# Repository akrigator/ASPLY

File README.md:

ASPLY
=====

Control block for  the 'Kronasteel Gala 600 inox' kitche hood based on atmega8/48/88/168/328 microcontroller

#Functions:
1. Manage light;
2. Manage 3 speed fan;
3. Adjustable timers for light and fan.

#Timer activation:
1. Hold one of channel button (light or fan speeds)  about 2,5 second till LED indicator starts blink (0.5 sec in turn on and 0.5 sec in turn off state);
2. Count 3 blinks of indicator to set timer for 30 minutes (each blink = 10 minutes);
3. Release the button - the channel function is activated, indicator blinks with low intencive (1 sec in turn on and 1 sec in turn off state) till timer is stopped;
4. Timer can be disabled by clicking same button again;

#Power cord pinout:
1. grey
2. brown
3. black - fan 3
4. blue - fan 2
5. red - fan 1
6. white - light

#Usefull link:
1. https://github.com/MCUdude/MiniCore - supporting of atmega 8/48/88/168 for ArduinoIDE;
2. https://github.com/dxinteractive/AnalogMultiButton - the library of buttons states and debouner for Arduino IDE.

#Flash atmega48:
1. Burn 'Arduino as ISP' sketch;
2. Pin Arduino board to atmega48 board on a breadboard;
3. Set Tools -> Programmer -> Arduino as ISP;
4. Set Tools -> Board -> Atmega48;
5. Set Tools -> Clock -> 8MHz internal;
6. Flash controller by Sketch -> Upload Using Programmer.

#Trouble shooting
If clear atmega48/88 is used and it works too slowly, you need to set correct fuse:

```
avrdude -c avrisp -p m48p -P /dev/cu.usbmodem1411 -b 19200 -U lfuse:w:0xE2:m -v
```

#Thanks for help
Виктор ! Михалин <vik-lab@mail.ru>

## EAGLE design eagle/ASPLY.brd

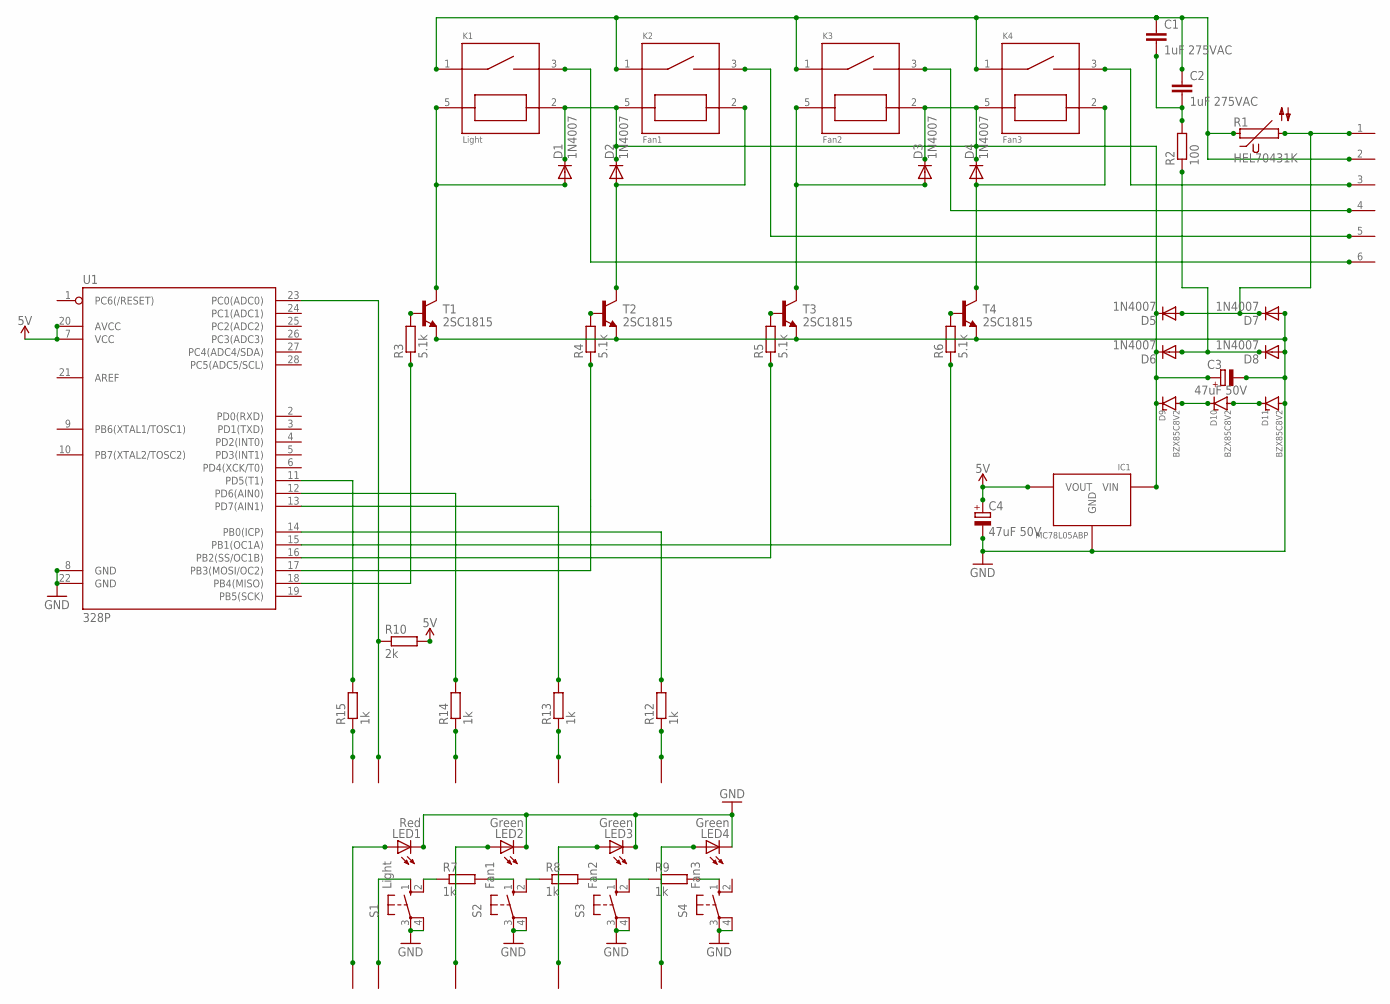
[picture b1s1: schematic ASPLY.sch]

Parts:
C1, C2: 1uF 275VAC; C22.5B8
C3, C4: 47uF 50V; E5-6
D1, D2, D3, D4, D5, D6, D7, D8: 1N4007; DO41-10
D9, D10, D11: BZX85C8V2; STAB
IC1: MC78L05ABP; TO-92
K1: Light; RELAY
K2: Fan1; RELAY
K3: Fan2; RELAY
K4: Fan3; RELAY
LED1: Red; LED3MM
LED2, LED3, LED4: Green; LED3MM
P1: MOLEX
R1: HEL70431K; S05K11
R2: 100; 0617/22
R3, R4, R5, R6: 5.1k; 0204/7
R7, R8, R9, R12, R13, R14, R15: 1k; 0204/7
R10: 2k; 0204/7
S1: Light; B3F-10XX
S2: Fan1; B3F-10XX
S3: Fan2; B3F-10XX
S4: Fan3; B3F-10XX
T1, T2, T3, T4: 2SC1815; TO92-ECB
U1: 328P; DIP28
U$1, U$3, U$5, U$7, U$8, U$13, U$14, U$16, U$18, U$20: PIN

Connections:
0: D5.A, D7.C, P1.1, R1.2
5V: C4.+, IC1.P$1 (VOUT), R10.2, U1.7 (VCC), U1.20 (AVCC)
24V: C3.+, D1.C, D2.C, D3.C, D4.C, D5.C, D6.C, D9.P$1, IC1.P$3 (VIN), K1.2, K2.5, K3.2, K4.5
220V: C1.1, C2.1, K1.1, K2.1, K3.1, K4.1, P1.2, R1.1
BUTTONS_INPUT: R10.1, U1.23 (PC0(ADC0)), U$8.P$1
GND: C3.-, C4.-, D7.A, D8.A, D11.P$2, IC1.P$2 (GND), LED1.K (C), LED2.K (C), LED3.K (C), LED4.K (C), S1.3, S1.4 (P1), S2.3, S2.4 (P1), S3.3, S3.4 (P1), S4.3, S4.4 (P1), T1.E, T2.E, T3.E, T4.E, U1.8 (GND), U1.22 (GND)
LED_FAN1: LED2.A, U$18.P$1
LED_FAN1_OUTPUT: R14.2, U1.12 (PD6(AIN0))
LED_FAN2: LED3.A, U$16.P$1
LED_FAN2_OUTPUT: R13.2, U1.13 (PD7(AIN1))
LED_FAN3: LED4.A, U$14.P$1
LED_FAN3_OUTPUT: R12.2, U1.14 (PB0(ICP))
LED_LIGHT: LED1.A, U$20.P$1
LED_LIGHT_OUTPUT: R15.2, U1.11 (PD5(T1))
unnamed: S1.1 (S), U$13.P$1
unnamed: K4.3, P1.3
unnamed: K3.3, P1.4
unnamed: K2.3, P1.5
unnamed: K1.3, P1.6
unnamed: R7.1, S1.2 (S1)
unnamed: R6.1, U1.15 (PB1(OC1A))
unnamed: R5.1, U1.16 (PB2(SS/OC1B))
unnamed: D1.A, K1.5, T1.C
unnamed: D2.A, K2.2, T2.C
unnamed: D3.A, K3.5, T3.C
unnamed: D4.A, K4.2, T4.C
unnamed: D6.A, D8.C, R2.1
unnamed: C1.2, C2.2, R2.2
unnamed: R7.2, S2.1 (S)
unnamed: D9.P$2, D10.P$1
unnamed: D10.P$2, D11.P$1
unnamed: R3.2, T1.B
unnamed: R4.2, T2.B
unnamed: R5.2, T3.B
unnamed: R6.2, T4.B
unnamed: R8.1, S2.2 (S1)
unnamed: R8.2, S3.1 (S)
unnamed: R9.1, S3.2 (S1)
unnamed: R9.2, S4.1 (S)
unnamed: R15.1, U$1.P$1
unnamed: R14.1, U$3.P$1
unnamed: R13.1, U$5.P$1
unnamed: R12.1, U$7.P$1
unnamed: R4.1, U1.17 (PB3(MOSI/OC2))
unnamed: R3.1, U1.18 (PB4(MISO))

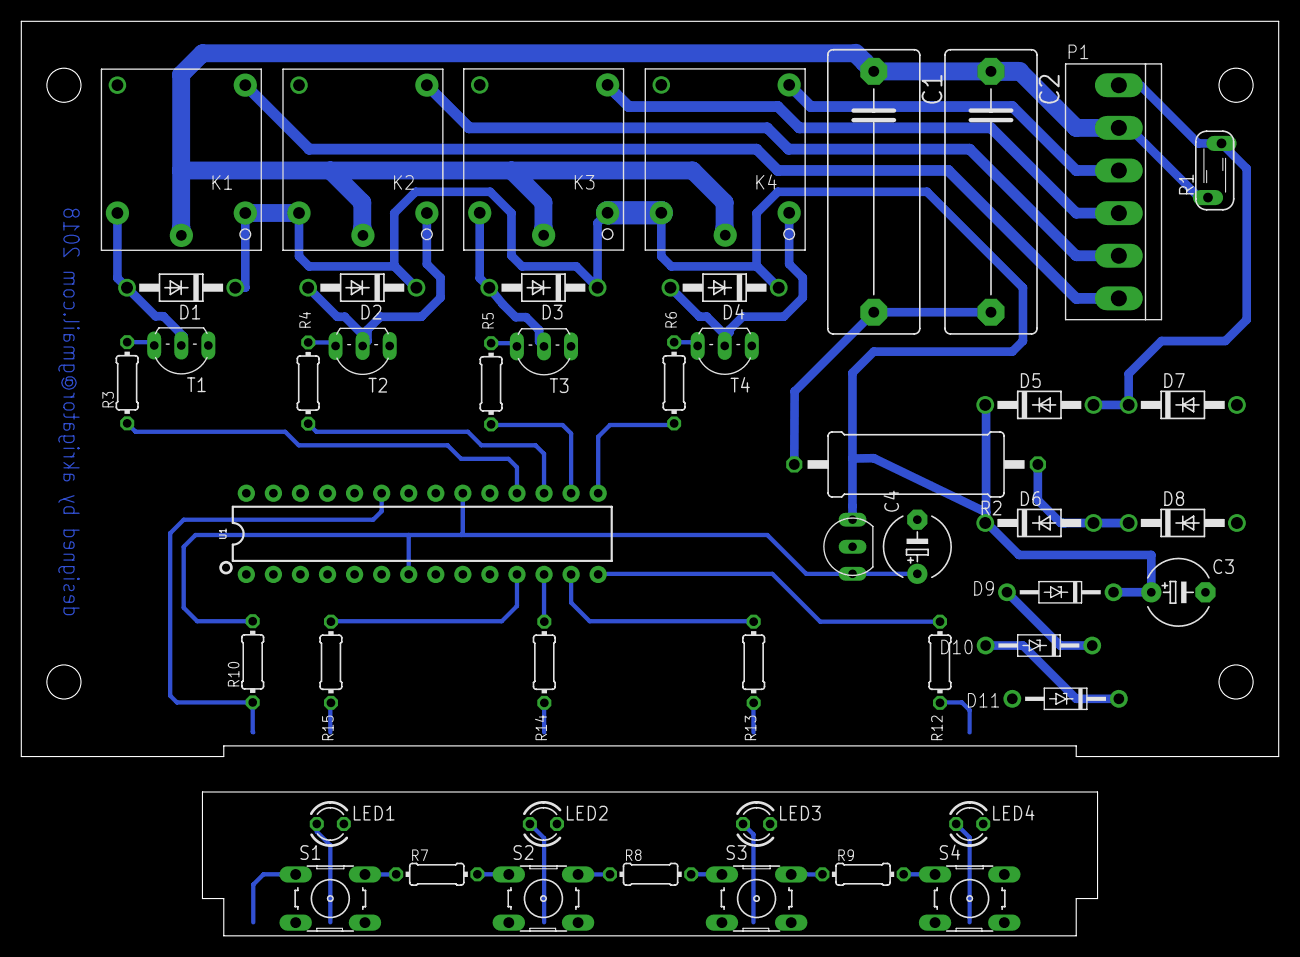
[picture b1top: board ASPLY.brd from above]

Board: 1 copper layer, 118.0 x 85.8 mm, 58 parts (0 on the bottom side), 45 nets.

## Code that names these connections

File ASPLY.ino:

#include <AnalogMultiButton.h>

#define BUTTONS_PIN A0
#define LED_LIGHT   5
#define LED_FAN1    6
#define LED_FAN2    7
#define LED_FAN3    8
#define CTRL_LIGHT  9
#define CTRL_FAN1   10
#define CTRL_FAN2   11
#define CTRL_FAN3   12

#define TIMER_ACTIVATION_DELAY 2500
#define TIMER_ACTIVATION_BLINK 500
#define TIMER_BLINK            1000
#define TIMER_BASE             600000

enum Channels {CHANNEL_LIGHT, CHANNEL_FAN1, CHANNEL_FAN2, CHANNEL_FAN3, CHANNELS_TOTAL};
const int BUTTONS_VALUES[CHANNELS_TOTAL] = {40, 343, 511, 613};

AnalogMultiButton buttons(BUTTONS_PIN, CHANNELS_TOTAL, BUTTONS_VALUES);

struct Output {
  const byte pin;
  unsigned long blink_timer;
  unsigned int blink_count;
  byte state;
  Output(byte pinv): pin(pinv), state(LOW), blink_timer(0), blink_count(0) {};
  void toggle(byte n_state) {state = n_state; digitalWrite(pin, state);};
  void on() {toggle(HIGH);};
  void off() {toggle(LOW); blink_count = 0;};
  void toggle() {toggle(state ? LOW : HIGH);};
  unsigned int blinking(unsigned long period) {
    unsigned long currentMillis = millis();
    if (currentMillis - blink_timer >= period) {
      blink_timer = currentMillis;
      toggle();
      blink_count++;
    }
    return blink_count/2;
  };
};

enum ChannelState {OFF, ON, TIMER_ACTIVATION, TIMER};

struct Channel {
  Output indicator;
  Output control;
  ChannelState state;
  unsigned long timer;
  unsigned int timer_multiply;
  
  Channel(byte led, byte ctrl): indicator(Output(led)), control(Output(ctrl)), state(OFF), timer(0) {
    pinMode(led, OUTPUT);
    pinMode(ctrl, OUTPUT);
  };
  void turnOn() {
    state = ON;
    indicator.on();
    control.on();
  };
  void turnOff() {
    state = OFF;
    indicator.off();
    control.off();
  };
  void timerActivation() {state = TIMER_ACTIVATION; indicator.blinking(TIMER_ACTIVATION_BLINK);};
  void startTimer() {state = TIMER; timer_multiply = indicator.blinking(TIMER_BLINK); control.on(); timer = millis();};
  void toggle() {
    if (state == OFF)
      turnOn();
    else 
      turnOff();
  };
  void tick() {
    unsigned long currentMillis = millis();
    if (timer > 0 && currentMillis - timer >= (timer_multiply * TIMER_BASE)) {
      timer = 0;
      turnOff();
    }
  };
  void update() {if (state > ON) {indicator.blinking(TIMER_BLINK); tick();}};
};

struct {
  Channel channels [CHANNELS_TOTAL] = {
    Channel(LED_LIGHT, CTRL_LIGHT),
    Channel(LED_FAN1, CTRL_FAN1),
    Channel(LED_FAN2, CTRL_FAN2),
    Channel(LED_FAN3, CTRL_FAN3)
  };
  void turnOffFans(byte j) {
    if (j != CHANNEL_LIGHT) {
      for (byte i = CHANNEL_FAN1; i < CHANNELS_TOTAL; i++) if (j != i) channels[i].turnOff();
    }
  };
} asply;

void setup() {}

void loop() {
  buttons.update();
  
  for (byte i = 0; i < CHANNELS_TOTAL; i++) {

    if (buttons.isPressed(i)) {
      if (buttons.isPressedAfter(i, TIMER_ACTIVATION_DELAY))
        asply.channels[i].timerActivation();
      else
        asply.channels[i].indicator.on();
    }

    if (buttons.onReleaseAfter(i, TIMER_ACTIVATION_DELAY)) {
      if (asply.channels[i].state != TIMER) {
        asply.turnOffFans(i);
        asply.channels[i].startTimer();
      }
    } else if (buttons.onRelease(i)) {
      asply.turnOffFans(i);
      asply.channels[i].toggle();
    }
    
    asply.channels[i].update();
  }

  delay(10);
}

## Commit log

2014-03-16 Ready to production
    ASPLY.ino с помощью Arduino Uno заливается на attiny45, плата
    изготавливается ЛУТом (ASPLY.pdf)
2014-06-01 fix schema
    The connection of emitter and collector are fixed. Increase in current
    limiting resistors of transistors from 2 to 10 kOm
2014-06-07 voltage debounce
2018-03-04 New FW revision:
    - Add timers per each channels;
    - Timer depends on the switch holding time (count of indictor blnks * 10
    minutes).
2018-03-04 New HW revision:
    - Split LED and transistor manage
2018-03-06 Update docs
2018-03-26 Setup power supply

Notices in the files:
parts and their libraries:
SparkFun-IC-Microcontroller: Licensing: Creative Commons ShareAlike 4.0 International - https://creativecommons.org/licenses/by-sa/4.0
